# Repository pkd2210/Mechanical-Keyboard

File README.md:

A 75$ 80$ keyboard, built using raspberry pi Pico.
The keyboard is a matrix of switches, I built it to learn how to use matrixes and build keyboards (as my previous attempt was a failier)

|Item       |Amount|Price|total price|link                                                                                                                                                                                                                                                                                                                                                                                                                                                                                                                                                                                                                                          |Notes                                                                                                                  |
|-----------|------|-----|-----------|----------------------------------------------------------------------------------------------------------------------------------------------------------------------------------------------------------------------------------------------------------------------------------------------------------------------------------------------------------------------------------------------------------------------------------------------------------------------------------------------------------------------------------------------------------------------------------------------------------------------------------------------|-----------------------------------------------------------------------------------------------------------------------|
|MX SWITCHES|1     |14.42|14.42      |https://www.aliexpress.com/item/1005004285423123.html?spm=a2g0o.productlist.main.5.4eb33cf2jI1Z2e&algo_pvid=6b9c4031-8745-4780-a49e-665a53c43b6b&algo_exp_id=6b9c4031-8745-4780-a49e-665a53c43b6b-4&pdp_ext_f=%7B%22order%22%3A%223132%22%2C%22eval%22%3A%221%22%2C%22fromPage%22%3A%22search%22%7D&pdp_npi=6%40dis%21ILS%2148.57%2146.03%21%21%2114.17%2113.43%21%40212a70c117586545414373866ec4cf%2112000028628937412%21sea%21IL%211913367454%21X%211%210%21n_tag%3A-29919%3Bd%3Ab5a670b1%3Bm03_new_user%3A-29895&curPageLogUid=4nw2h3mTUMKV&utparam-url=scene%3Asearch%7Cquery_from%3A%7Cx_object_id%3A1005004285423123%7C_p_origin_prod%3A|Total is 110 pcs because it’s the cheapest, and I know I will burn or destroy a few of them in the way, Dustproof Green|
|Diodes     |1     |2.63 |2.63       |https://www.aliexpress.com/item/32488957012.html?spm=a2g0o.productlist.main.5.30f86763rDJdg3&algo_pvid=01e23c32-b637-4162-a303-f14a932611e7&algo_exp_id=01e23c32-b637-4162-a303-f14a932611e7-4&pdp_ext_f=%7B%22order%22%3A%223%22%2C%22eval%22%3A%221%22%2C%22fromPage%22%3A%22search%22%7D&pdp_npi=6%40dis%21USD%212.73%212.73%21%21%212.73%212.73%21%40210123bc17586548230864157e1172%2156791789356%21sea%21IL%211913367454%21X%211%210%21n_tag%3A-29919%3Bd%3Ab5a670b1%3Bm03_new_user%3A-29895&curPageLogUid=hM4toNCWTDJ6&utparam-url=scene%3Asearch%7Cquery_from%3A%7Cx_object_id%3A32488957012%7C_p_origin_prod%3A                       |Its for 200 pcs but I couldn’t find a pack of 100 normal diodes                                                        |
|RPI2040    |1     |3.05 |3.05       |https://www.aliexpress.com/item/1005008948799927.html?spm=a2g0o.productlist.main.1.674a109500HQ1g&algo_pvid=7a79b1ca-94fd-4140-accd-9f61e0617cf5&algo_exp_id=7a79b1ca-94fd-4140-accd-9f61e0617cf5-0&pdp_ext_f=%7B%22order%22%3A%22330%22%2C%22eval%22%3A%221%22%2C%22fromPage%22%3A%22search%22%7D&pdp_npi=6%40dis%21USD%212.95%212.95%21%21%2120.91%2120.91%21%402141115b17586549705312321e97cd%2112000047322739294%21sea%21IL%211913367454%21X%211%210%21n_tag%3A-29919%3Bd%3Ab5a670b1%3Bm03_new_user%3A-29895&curPageLogUid=HPL7e0igKT7u&utparam-url=scene%3Asearch%7Cquery_from%3A%7Cx_object_id%3A1005008948799927%7C_p_origin_prod%3A   |Pico Type-c Welding                                                                                                    |
|PCB        |1     |51.77|51.77      |                                                                                                                                                                                                                                                                                                                                                                                                                                                                                                                                                                                                                                              |                                                                                                                       |
|           |      |     |0          |                                                                                                                                                                                                                                                                                                                                                                                                                                                                                                                                                                                                                                              |                                                                                                                       |
|           |      |     |0          |                                                                                                                                                                                                                                                                                                                                                                                                                                                                                                                                                                                                                                              |                                                                                                                       |
|           |      |     |0          |                                                                                                                                                                                                                                                                                                                                                                                                                                                                                                                                                                                                                                              |                                                                                                                       |
|           |      |     |0          |                                                                                                                                                                                                                                                                                                                                                                                                                                                                                                                                                                                                                                              |                                                                                                                       |
|           |      |     |0          |                                                                                                                                                                                                                                                                                                                                                                                                                                                                                                                                                                                                                                              |                                                                                                                       |

The keyboard i quite simple, with no cover or specific keycaps, beacuse i planed it to be customizwable with any case you want online, and any keycaps you want online.

Personaly i'm gonna try to make a case out of wood, and order wood themed keycaps.
# Update
* Updated the pcb layout to use a diffrent tkl layout, now with kleplacer and not manually (As Requested by my stasis reviewer)
new image:

* Remade the case

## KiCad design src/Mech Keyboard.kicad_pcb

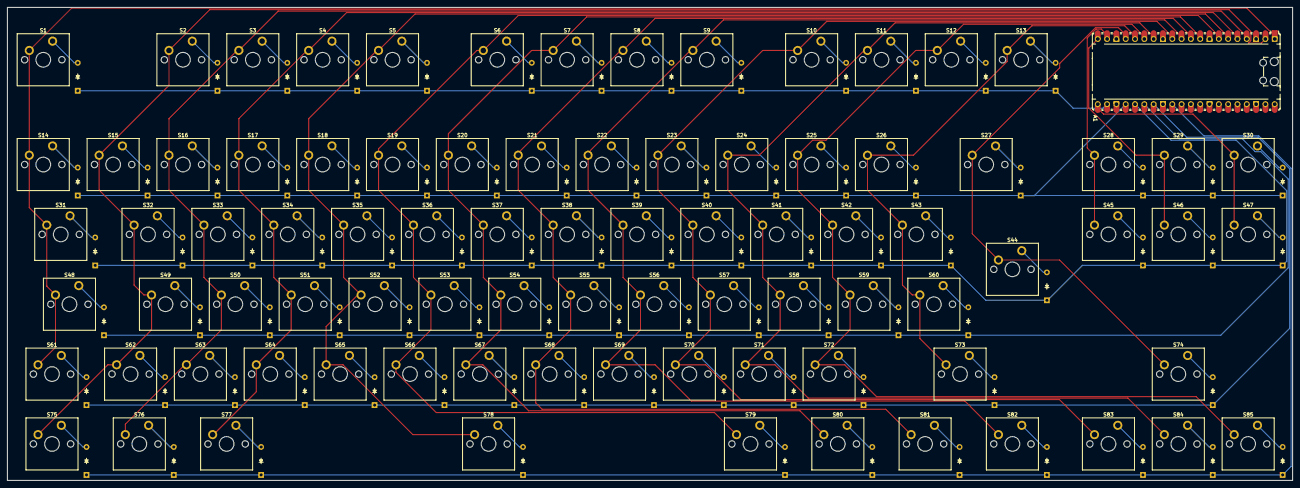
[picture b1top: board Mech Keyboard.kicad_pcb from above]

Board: 2 copper layers, 350.5 x 129.0 mm, 171 parts (0 on the bottom side), 109 nets.

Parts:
A1: RaspberryPi_Pico; RaspberryPi_Pico_Common_Unspecified
D1, D2, D3, D4, D5, D6, D7, D8, D9, D10, D11, D12, D13, D14, D15, D16, D17, D18, D19, D20, D21, D22, D23, D24, D25, D26, D27, D28, D29, D30, D31, D32, D33, D34, D35, D36, D37, D38, D39, D40, D41, D42, D43, D44, D45, D46, D47, D48, D49, D50, D51, D52, D53, D54, D55, D56, D57, D58, D59, D60, D61, D62, D63, D64, D65, D66, D67, D68, D69, D70, D71, D72, D73, D74, D75, D76, D77, D78, D79, D80, D81, D82, D83, D84, D85: Diode; Diode_DO-35
S1, S2, S3, S4, S5, S6, S7, S8, S9, S10, S11, S12, S13, S14, S15, S16, S17, S18, S19, S20, S21, S22, S23, S24, S25, S26, S27, S28, S29, S30, S31, S32, S33, S34, S35, S36, S37, S38, S39, S40, S41, S42, S43, S44, S45, S46, S47, S48, S49, S50, S51, S52, S53, S54, S55, S56, S57, S58, S59, S60, S61, S62, S63, S64, S65, S66, S67, S68, S69, S70, S71, S72, S73, S74, S75, S76, S77, S78, S79, S80, S81, S82, S83, S84, S85: Keyswitch; MX_PCB_1.00u

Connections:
Column 0: A1.1 (GPIO0), S1.1, S14.1, S31.1, S48.1, S61.1
Column 1: A1.2 (GPIO1), S2.1, S15.1, S32.1, S49.1, S62.1, S75.1
Column 2: A1.4 (GPIO2), S3.1, S16.1, S33.1, S50.1, S63.1, S76.1
Column 3: A1.5 (GPIO3), S4.1, S17.1, S34.1, S51.1, S64.1, S77.1
Column 4: A1.6 (GPIO4), S5.1, S18.1, S35.1, S52.1, S65.1, S78.1
Column 5: A1.7 (GPIO5), S6.1, S19.1, S36.1, S53.1, S66.1, S79.1
Column 6: A1.9 (GPIO6), S7.1, S20.1, S37.1, S54.1, S67.1, S80.1
Column 7: A1.10 (GPIO7), S8.1, S21.1, S38.1, S55.1, S68.1, S81.1
Column 8: A1.11 (GPIO8), S9.1, S22.1, S39.1, S56.1, S69.1, S82.1
Column 9: A1.12 (GPIO9), S10.1, S23.1, S40.1, S57.1, S70.1, S83.1
Column 10: A1.14 (GPIO10), S11.1, S24.1, S41.1, S58.1, S71.1, S84.1
Column 11: A1.15 (GPIO11), S12.1, S25.1, S42.1, S59.1, S72.1, S85.1
Column 12: A1.16 (GPIO12), S13.1, S26.1, S43.1, S60.1, S73.1
Column 13: A1.17 (GPIO13), S27.1, S44.1, S74.1
Column 14: A1.19 (GPIO14), S28.1, S45.1
Column 15: A1.20 (GPIO15), S29.1, S46.1
Column 16: A1.21 (GPIO16), S30.1, S47.1
unnamed: A1.3 (GND), A1.8 (GND), A1.13 (GND), A1.18 (GND), A1.23 (GND), A1.28 (GND), A1.38 (GND)
unnamed: D1.2 (A), S1.2
unnamed: D2.2 (A), S2.2
unnamed: D3.2 (A), S3.2
unnamed: D4.2 (A), S4.2
unnamed: D5.2 (A), S5.2
unnamed: D6.2 (A), S6.2
unnamed: D7.2 (A), S7.2
unnamed: D8.2 (A), S8.2
unnamed: D9.2 (A), S9.2
unnamed: D10.2 (A), S10.2
unnamed: D11.2 (A), S11.2
unnamed: D12.2 (A), S12.2
unnamed: D13.2 (A), S13.2
unnamed: D14.2 (A), S14.2
unnamed: D15.2 (A), S15.2
unnamed: D16.2 (A), S16.2
unnamed: D17.2 (A), S17.2
unnamed: D18.2 (A), S18.2
unnamed: D19.2 (A), S19.2
unnamed: D20.2 (A), S20.2
unnamed: D21.2 (A), S21.2
unnamed: D22.2 (A), S22.2
unnamed: D23.2 (A), S23.2
unnamed: D24.2 (A), S24.2
unnamed: D25.2 (A), S25.2
unnamed: D26.2 (A), S26.2
unnamed: D27.2 (A), S27.2
unnamed: D28.2 (A), S28.2
unnamed: D29.2 (A), S29.2
unnamed: D30.2 (A), S30.2
unnamed: D31.2 (A), S31.2
unnamed: D32.2 (A), S32.2
unnamed: D33.2 (A), S33.2
unnamed: D34.2 (A), S34.2
unnamed: D35.2 (A), S35.2
unnamed: D36.2 (A), S36.2
unnamed: D37.2 (A), S37.2
unnamed: D38.2 (A), S38.2
unnamed: D39.2 (A), S39.2
unnamed: D40.2 (A), S40.2
unnamed: D41.2 (A), S41.2
unnamed: D42.2 (A), S42.2
unnamed: D43.2 (A), S43.2
unnamed: D44.2 (A), S44.2
unnamed: D45.2 (A), S45.2
unnamed: D46.2 (A), S46.2
unnamed: D47.2 (A), S47.2
unnamed: D48.2 (A), S48.2
unnamed: D49.2 (A), S49.2
unnamed: D50.2 (A), S50.2
unnamed: D51.2 (A), S51.2
unnamed: D52.2 (A), S52.2
unnamed: D53.2 (A), S53.2
unnamed: D54.2 (A), S54.2
unnamed: D55.2 (A), S55.2
unnamed: D56.2 (A), S56.2
unnamed: D57.2 (A), S57.2
unnamed: D58.2 (A), S58.2
unnamed: D59.2 (A), S59.2
unnamed: D60.2 (A), S60.2
unnamed: D61.2 (A), S61.2
unnamed: D62.2 (A), S62.2
unnamed: D63.2 (A), S63.2
unnamed: D64.2 (A), S64.2
unnamed: D65.2 (A), S65.2
unnamed: D66.2 (A), S66.2
unnamed: D67.2 (A), S67.2
unnamed: D68.2 (A), S68.2
unnamed: D69.2 (A), S69.2
unnamed: D70.2 (A), S70.2
unnamed: D71.2 (A), S71.2
unnamed: D72.2 (A), S72.2
unnamed: D73.2 (A), S73.2
unnamed: D74.2 (A), S74.2
unnamed: D75.2 (A), S75.2
unnamed: D76.2 (A), S76.2
unnamed: D77.2 (A), S77.2
unnamed: D78.2 (A), S78.2
unnamed: D79.2 (A), S79.2
unnamed: D80.2 (A), S80.2
unnamed: D81.2 (A), S81.2
unnamed: D82.2 (A), S82.2
unnamed: D83.2 (A), S83.2
unnamed: D84.2 (A), S84.2
unnamed: D85.2 (A), S85.2
Row 0: A1.22 (GPIO17), D1.1 (K), D2.1 (K), D3.1 (K), D4.1 (K), D5.1 (K), D6.1 (K), D7.1 (K), D8.1 (K), D9.1 (K), D10.1 (K), D11.1 (K), D12.1 (K), D13.1 (K)
Row 1: A1.24 (GPIO18), D14.1 (K), D15.1 (K), D16.1 (K), D17.1 (K), D18.1 (K), D19.1 (K), D20.1 (K), D21.1 (K), D22.1 (K), D23.1 (K), D24.1 (K), D25.1 (K), D26.1 (K), D27.1 (K), D28.1 (K), D29.1 (K), D30.1 (K)
Row 2: A1.25 (GPIO19), D31.1 (K), D32.1 (K), D33.1 (K), D34.1 (K), D35.1 (K), D36.1 (K), D37.1 (K), D38.1 (K), D39.1 (K), D40.1 (K), D41.1 (K), D42.1 (K), D43.1 (K), D44.1 (K), D45.1 (K), D46.1 (K), D47.1 (K)
Row 3: A1.26 (GPIO20), D48.1 (K), D49.1 (K), D50.1 (K), D51.1 (K), D52.1 (K), D53.1 (K), D54.1 (K), D55.1 (K), D56.1 (K), D57.1 (K), D58.1 (K), D59.1 (K), D60.1 (K)
Row 4: A1.27 (GPIO21), D61.1 (K), D62.1 (K), D63.1 (K), D64.1 (K), D65.1 (K), D66.1 (K), D67.1 (K), D68.1 (K), D69.1 (K), D70.1 (K), D71.1 (K), D72.1 (K), D73.1 (K), D74.1 (K)
Row 5: A1.29 (GPIO22), D75.1 (K), D76.1 (K), D77.1 (K), D78.1 (K), D79.1 (K), D80.1 (K), D81.1 (K), D82.1 (K), D83.1 (K), D84.1 (K), D85.1 (K)

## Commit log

2025-09-12 Current files
2025-10-23 add bom
2025-10-23 Refine keyboard layout description in JOURNAL.mdupdate
    Removed redundant text and clarified layout description.
2025-10-24 Revise README with project details and customization plansrea
    Updated README to provide detailed information about the keyboard project, including pricing, components, and personal plans for customization.
2025-10-24 gerber
2025-10-24 pcb model
2025-10-24 Added case model
2026-05-10 Update to include new pcb
2026-05-10 Add image from new layout
2026-05-10 Add step file
2026-05-11 Add new cads
2026-05-11 Upload new case readme
2026-05-11 Add kle
